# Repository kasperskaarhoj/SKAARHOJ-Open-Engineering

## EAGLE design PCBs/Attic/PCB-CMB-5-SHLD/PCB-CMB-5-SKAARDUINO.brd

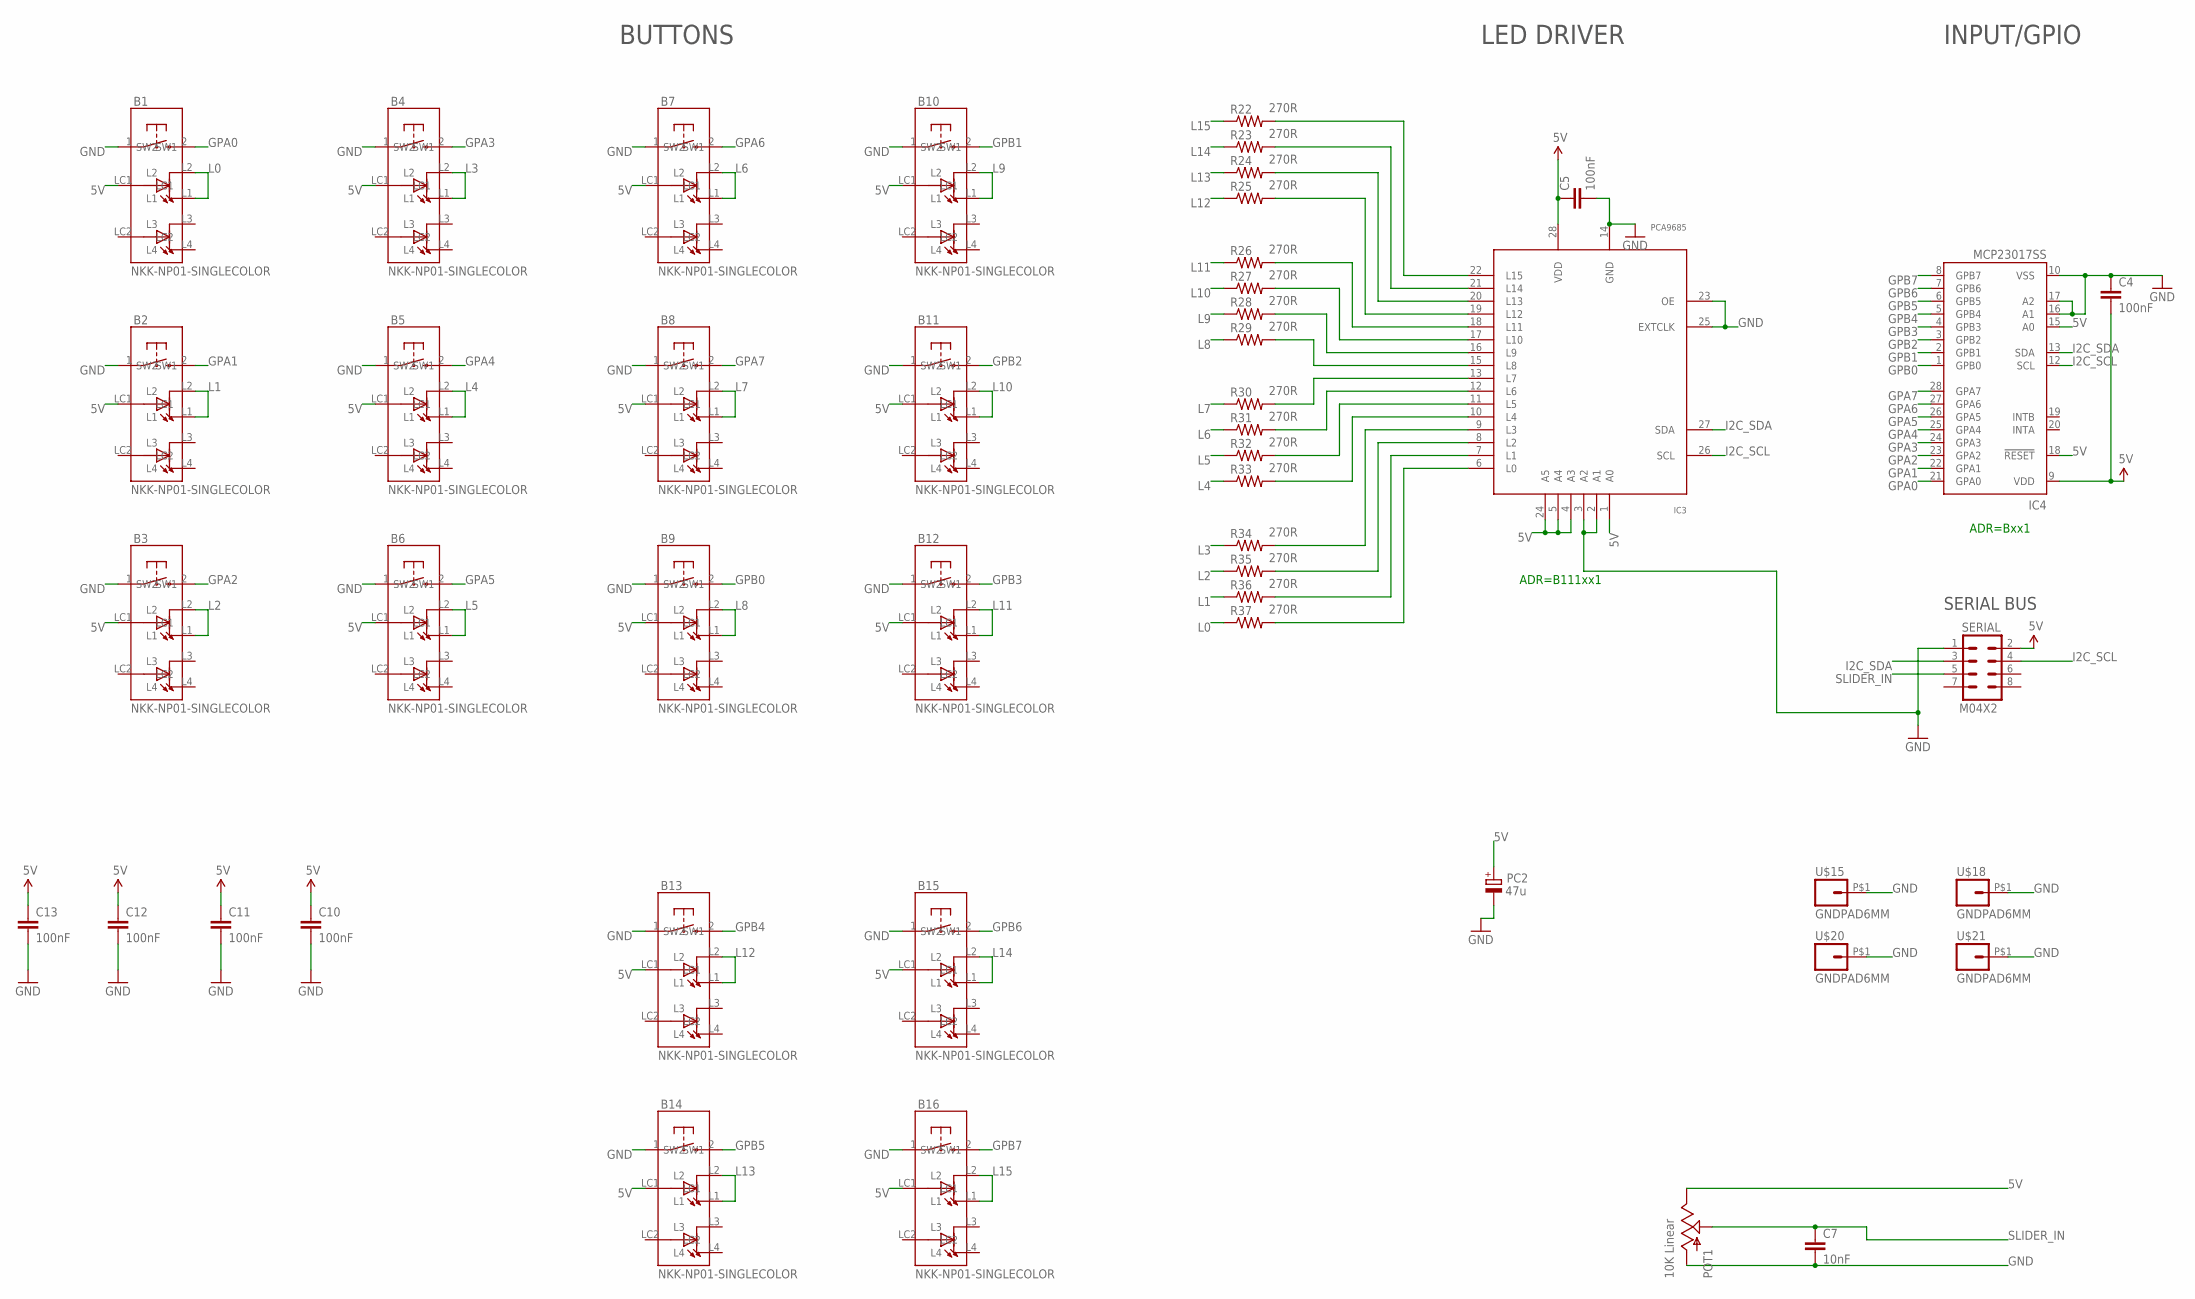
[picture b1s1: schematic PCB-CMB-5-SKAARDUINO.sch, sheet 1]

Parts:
B1, B2, B3, B4, B5, B6, B7, B8, B9, B10, B11, B12, B13, B14, B15, B16: NKK-NP01-SINGLECOLOR; NKK-NP01
C4, C5, C10, C11, C12, C13: 100nF; 0603-CAP
C7: 10nF; 0603-CAP
IC3: PCA9685; TSSOP28
IC4: MCP23017SS; SSOP28; MPN MCP23017-E/SS
PC2: 47u; PANASONIC_D
POT1: 10K Linear; SLIDER20
R22, R23, R24, R25, R26, R27, R28, R29, R30, R31, R32, R33, R34, R35, R36, R37: 270R; 0603-RES
SERIAL: M04X2; 2X4
U$15, U$18, U$20, U$21: GNDPAD6MM; 3.2MMPAD6MM

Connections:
5V: B1.LC1, B2.LC1, B3.LC1, B4.LC1, B5.LC1, B6.LC1, B7.LC1, B8.LC1, B9.LC1, B10.LC1, B11.LC1, B12.LC1, B13.LC1, B14.LC1, B15.LC1, B16.LC1, C4.2, C5.1, C10.1, C11.1, C12.1, C13.1, IC3.1 (A0), IC3.4 (A3), IC3.5 (A4), IC3.24 (A5), IC3.28 (VDD), IC4.9 (VDD), IC4.15 (A0), IC4.18 (!RESET), PC2.+, POT1.1 (E), SERIAL.2
GND: B1.1 (SW1), B2.1 (SW1), B3.1 (SW1), B4.1 (SW1), B5.1 (SW1), B6.1 (SW1), B7.1 (SW1), B8.1 (SW1), B9.1 (SW1), B10.1 (SW1), B11.1 (SW1), B12.1 (SW1), B13.1 (SW1), B14.1 (SW1), B15.1 (SW1), B16.1 (SW1), C4.1, C5.2, C7.2, C10.2, C11.2, C12.2, C13.2, IC3.2 (A1), IC3.3 (A2), IC3.14 (GND), IC3.23 (OE), IC3.25 (EXTCLK), IC4.10 (VSS), IC4.16 (A1), IC4.17 (A2), PC2.-, POT1.3 (A), SERIAL.1, U$15.P$1, U$18.P$1, U$20.P$1, U$21.P$1
GPA0: B1.2 (SW2), IC4.21 (GPA0)
GPA1: B2.2 (SW2), IC4.22 (GPA1)
GPA2: B3.2 (SW2), IC4.23 (GPA2)
GPA3: B4.2 (SW2), IC4.24 (GPA3)
GPA4: B5.2 (SW2), IC4.25 (GPA4)
GPA5: B6.2 (SW2), IC4.26 (GPA5)
GPA6: B7.2 (SW2), IC4.27 (GPA6)
GPA7: B8.2 (SW2), IC4.28 (GPA7)
GPB0: B9.2 (SW2), IC4.1 (GPB0)
GPB1: B10.2 (SW2), IC4.2 (GPB1)
GPB2: B11.2 (SW2), IC4.3 (GPB2)
GPB3: B12.2 (SW2), IC4.4 (GPB3)
GPB4: B13.2 (SW2), IC4.5 (GPB4)
GPB5: B14.2 (SW2), IC4.6 (GPB5)
GPB6: B15.2 (SW2), IC4.7 (GPB6)
GPB7: B16.2 (SW2), IC4.8 (GPB7)
I2C_SCL: IC3.26 (SCL), IC4.12 (SCL), SERIAL.4
I2C_SDA: IC3.27 (SDA), IC4.13 (SDA), SERIAL.3
L0: B1.L1, B1.L2, R37.1
L1: B2.L1, B2.L2, R36.1
L2: B3.L1, B3.L2, R35.1
L3: B4.L1, B4.L2, R34.1
L4: B5.L1, B5.L2, R33.1
L5: B6.L1, B6.L2, R32.1
L6: B7.L1, B7.L2, R31.1
L7: B8.L1, B8.L2, R30.1
L8: B9.L1, B9.L2, R29.1
L9: B10.L1, B10.L2, R28.1
L10: B11.L1, B11.L2, R27.1
L11: B12.L1, B12.L2, R26.1
L12: B13.L1, B13.L2, R25.1
L13: B14.L1, B14.L2, R24.1
L14: B15.L1, B15.L2, R23.1
L15: B16.L1, B16.L2, R22.1
unnamed: IC3.13 (L7), R30.2
unnamed: IC3.12 (L6), R31.2
unnamed: IC3.11 (L5), R32.2
unnamed: IC3.10 (L4), R33.2
unnamed: IC3.9 (L3), R34.2
unnamed: IC3.8 (L2), R35.2
unnamed: IC3.7 (L1), R36.2
unnamed: IC3.6 (L0), R37.2
unnamed: IC3.15 (L8), R29.2
unnamed: IC3.16 (L9), R28.2
unnamed: IC3.17 (L10), R27.2
unnamed: IC3.18 (L11), R26.2
unnamed: IC3.19 (L12), R25.2
unnamed: IC3.20 (L13), R24.2
unnamed: IC3.21 (L14), R23.2
unnamed: IC3.22 (L15), R22.2
SLIDER_IN: C7.1, POT1.2A (S), SERIAL.5

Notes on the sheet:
ADR=B111xx1
ADR=Bxx1
BUTTONS
LED DRIVER
INPUT/GPIO
SERIAL BUS

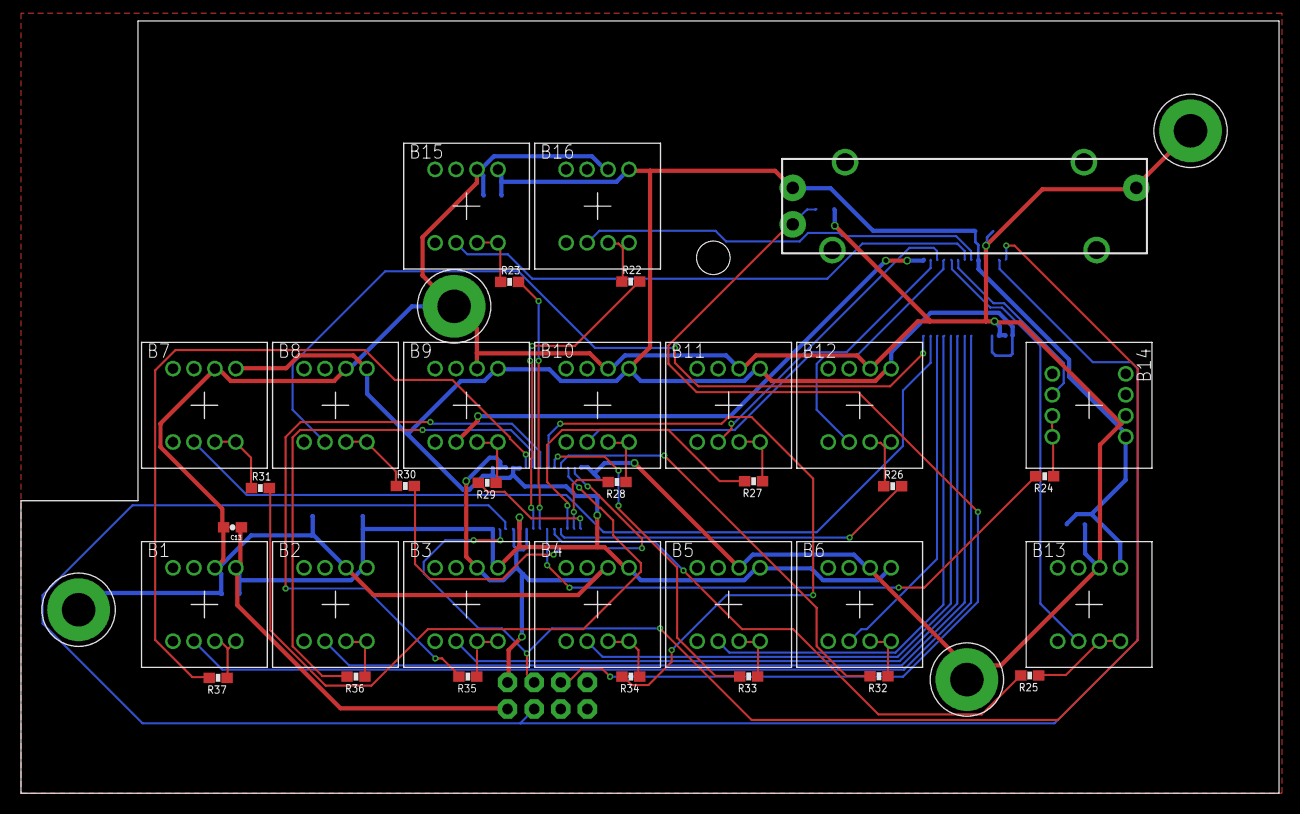
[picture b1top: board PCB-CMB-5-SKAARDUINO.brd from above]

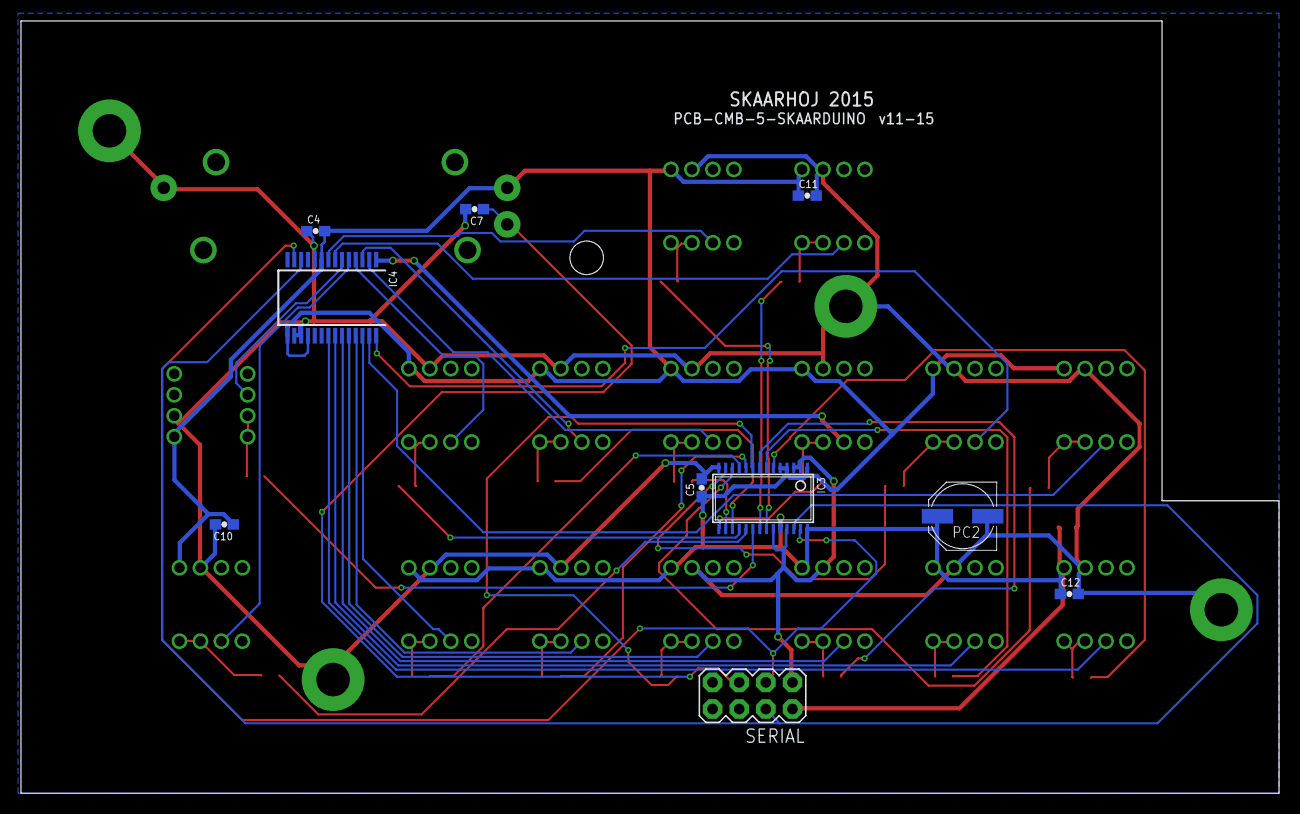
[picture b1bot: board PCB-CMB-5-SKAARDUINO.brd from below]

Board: 2 copper layers, 120.0 x 73.7 mm, 48 parts (10 on the bottom side), 53 nets.

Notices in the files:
parts and their libraries:
SparkFun: Licensing: CC v3.0 Share-Alike You are welcome to use this library for commercial purposes.
